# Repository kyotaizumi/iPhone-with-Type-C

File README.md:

# iPhone-with-Type-C
iPhone to Type-C project.

## DEMO Video

https://youtu.be/KHqov9P1oOM?t=35

## Photo of PCB

## PCB 3D viewer

I use KiCad, PCB Way.

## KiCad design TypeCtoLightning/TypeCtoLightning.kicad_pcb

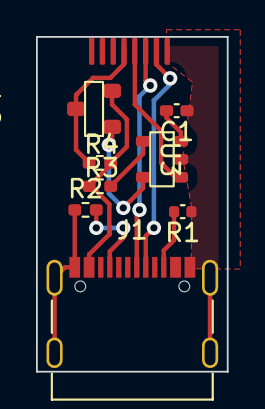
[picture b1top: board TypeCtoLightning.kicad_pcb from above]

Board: 2 copper layers, 10.6 x 18.6 mm, 9 parts (0 on the bottom side), 11 nets.

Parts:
C1: C; C_0402_1005Metric_Pad0.74x0.62mm_HandSolder
J1: USB_C_Receptacle_USB2.0; USB_C_Receptacle_Palconn_UTC16-G
R1: 5.12k; C_0402_1005Metric
R2: 5.12k; R_0402_1005Metric_Pad0.72x0.64mm_HandSolder
R3, R4: R; R_0402_1005Metric_Pad0.72x0.64mm_HandSolder
U2: LightningPlug8Pin; Lightning
U3: AD509; USBTypeCtoLightinngMosfet
U4: 3415; USBTypeCtoLightning3415

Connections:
unnamed: C1.1, J1.A1 (GND), J1.A12 (GND), J1.B1 (GND), J1.B12 (GND), J1.S1 (SHIELD), R1.1, R2.1, U2.8 (GND), U3.2 (GND)
unnamed: C1.2, U3.1
unnamed: J1.A4 (VBUS), J1.A9 (VBUS), J1.B4 (VBUS), J1.B9 (VBUS), R3.2, R4.1, U4.2 (V+)
unnamed: J1.A5 (CC1), R2.2
unnamed: J1.A7 (D-), U2.6 (D-)
unnamed: J1.B5 (CC2), R1.2
unnamed: J1.B6 (D+), U2.7 (D+)
unnamed: R3.1, U3.4
unnamed: R4.2, U2.4 (V+), U4.3 (Vout)
unnamed: U2.5 (?), U3.3
unnamed: U3.6, U4.1
